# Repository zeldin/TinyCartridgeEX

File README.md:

WARNING
=======

This design is completely untested.  Since the TinyFPGA EX is not
actually available yet, there are also a number of open questions
such as:

* Does the width of the module match a standard DIL-48 socket?
  - Yes it does

* Is it OK to power the module by feeding +5V into the `Vin` pin,
  and use the `3v3` pin(s) to power auxilliary logic?  (I would
  assume so, but needs to be verified.)
  - Seems legit.  The DC/DC for 3.3V works with input voltage down
    to 3.8V, so add a protection diode with Vf < 1V.

* Are all the 42 numbered pins capable of 3.3V I/O (I sure hope so)?
  - Accoring to published schematics, VCCIO0-2 and VCCIO6-8 are all tied
  to 3.3V, which should cover all 42 pins.

TinyCartridge EX
================

The TinyCartridge EX is a carrier board for the upcoming
[TinyFPGA EX](https://www.crowdsupply.com/tinyfpga/tinyfpga-ex)
FPGA module in the form of a Commodore 64 cartridge.  All pins
on the C64 expansion port are directly available to the FPGA, with
the modification that `IO1` and `IO2` are reduced to a single
signal with NAND, and the same for `ROML` and `ROMH`.

The intention is to provide a platform for the
[super-reu](https://github.com/zeldin/super-reu) supported by
open toolchains (i.e. SymbiFlow).

Acknowledgements
----------------

The C64 expansion port and cartridge symbol and footprint were
designed by [RETRO Innovations](http://www.go4retro.com/).

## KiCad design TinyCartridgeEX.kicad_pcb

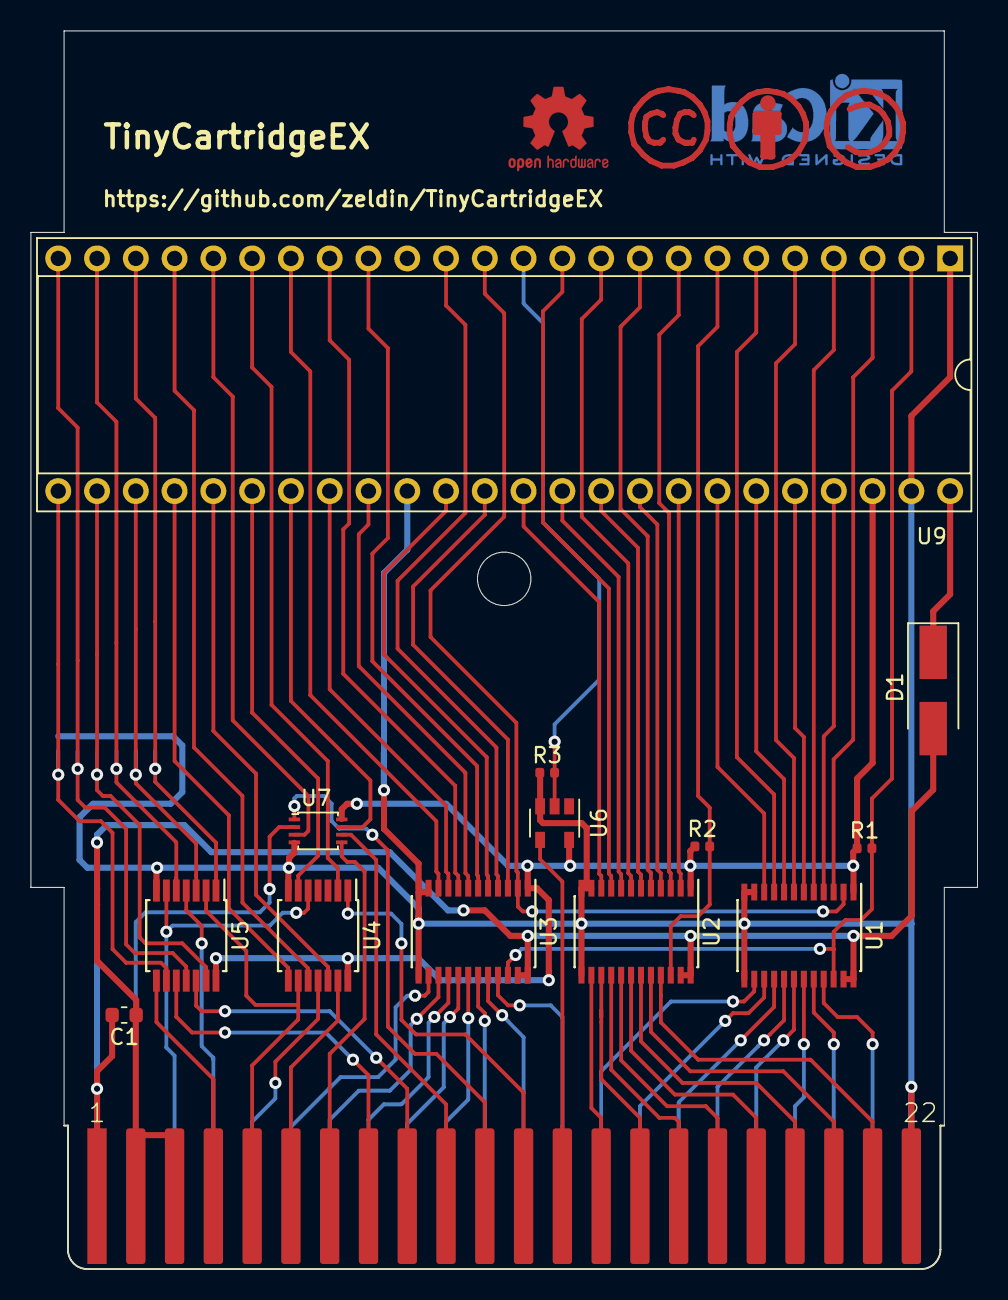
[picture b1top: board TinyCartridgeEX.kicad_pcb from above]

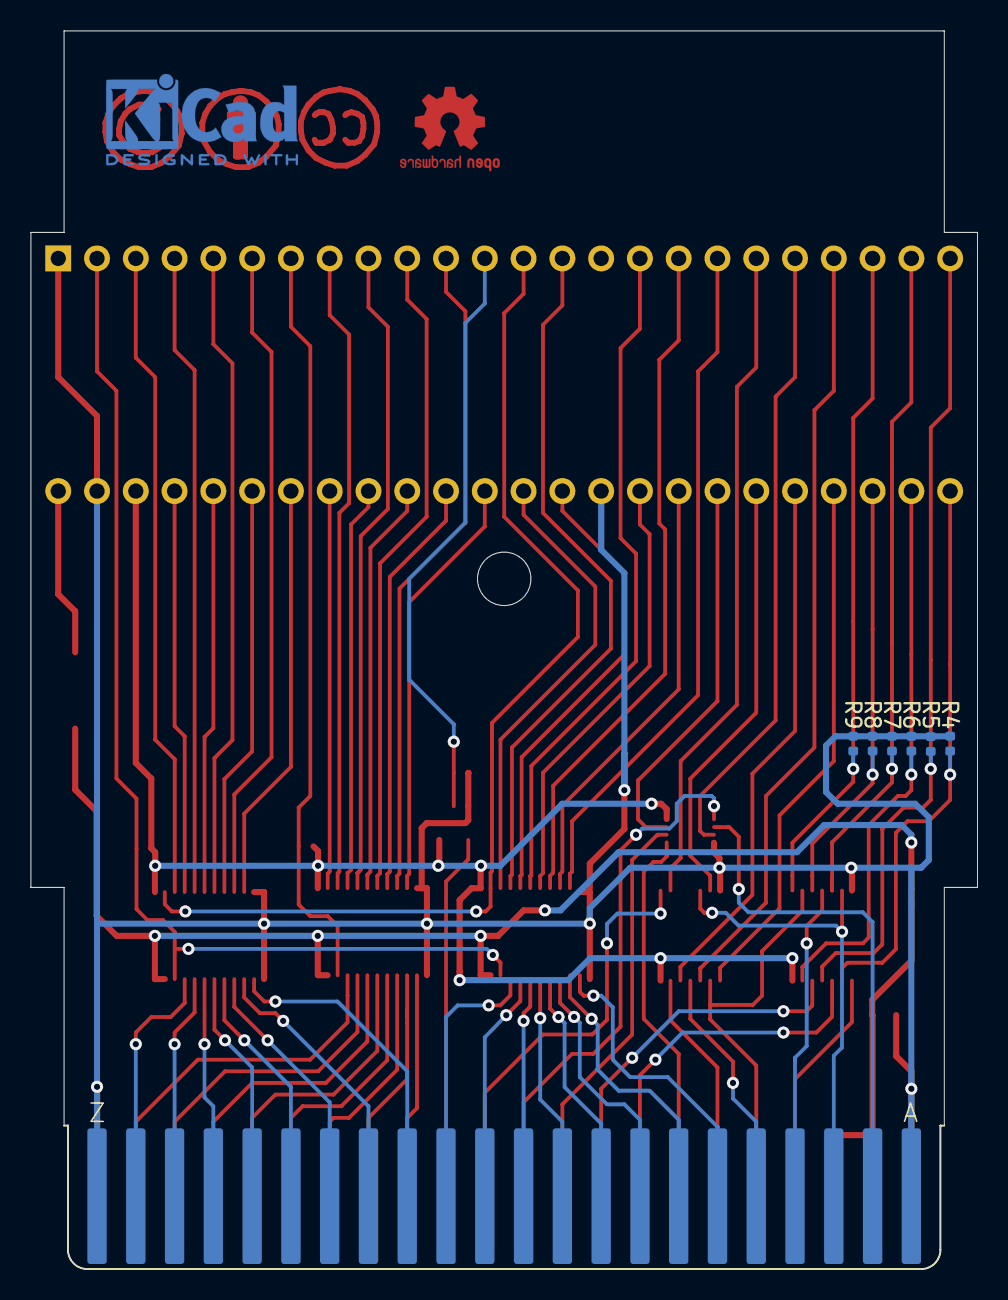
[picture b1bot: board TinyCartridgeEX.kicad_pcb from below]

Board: 2 copper layers, 62.0 x 81.1 mm, 28 parts (7 on the bottom side), 84 nets.

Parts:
C1: 0.1u; C_0603_1608Metric
CART1: CARTRIDGE_C64; CARTRIDGE_C64_GERMAN
D1: EC30QSA045; D_SMA_Handsoldering
J1, J2: Conn_01x24; PinHeader_1x24_P2.54mm_Vertical_UpsideDown
R1, R2, R3, R4, R5, R6, R7, R8, R9: 4.7k; R_0402_1005Metric
REFBY: Symbol_CC-Attribution_CopperTop_Small
REFCC: Symbol_CreativeCommons_CopperTop_Type2_Small
REFKI: KiCad-Logo2_5mm_Copper
REFOSHW: OSHW-Logo2_7.3x6mm_Copper
REFSA: Symbol_CC-ShareAlike_CopperTop_Small
U1, U2, U3: SN74LVC8T245; TSSOP-24_4.4x7.8mm_P0.65mm
U4: 74LV17A; TSSOP-14_4.4x5mm_P0.65mm
U5: 74LVC06A; TSSOP-14_4.4x5mm_P0.65mm
U6: 74LVC1G06; SOT-23-5
U7: 74LVC2G132; VSSOP-8_2.4x2.1mm_P0.5mm
U9: TinyFPGA_EX
X1: EXPANSION_PORT_C64_EDGE; MA100-22-2

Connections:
+5V: C1.1, D1.2, U1.23, U1.24, U2.23, U2.24, U3.23, U3.24, X1.2, X1.3
/Level Shifters/8: U3.21, X1.P
/Level Shifters/9: U3.20, X1.N
/Level Shifters/10: U3.19, X1.M
/Level Shifters/11: U3.18, X1.L
/Level Shifters/12: U3.17, X1.K
/Level Shifters/13: U3.16, X1.J
/Level Shifters/14: U3.15, X1.H
/Level Shifters/15: U3.14, X1.F
A0: U1.3, U9.3
A1: U1.4, U9.45
A2: U1.5, U9.4
A3: U1.6, U9.44
A4: U1.7, U9.5
A5: U1.8, U9.43
A6: U1.9, U9.6
A7: U1.10, U9.42
A8: U3.3, U9.36
A9: U3.4, U9.14
A10: U3.5, U9.35
A11: U3.6, U9.16
A12: U3.7, U9.33
A13: U3.8, U9.17
A14: U3.9, U9.32
A15: U3.10, U9.18
A_DIR: U1.2, U3.2, U9.13
A_~EN: R1.2, U1.22, U3.22, U9.2
BA: U4.2, U9.19
D0: U2.3, U9.8
D1: U2.4, U9.40
D2: U2.5, U9.9
D3: U2.6, U9.39
D4: U2.7, U9.10
D5: U2.8, U9.38
D6: U2.9, U9.11
D7: U2.10, U9.37
DMA: R3.1, U6.2, U9.12
DOTCLK: U4.12, U9.29
D_DIR: U2.2, U9.41
D_~EN: R2.1, U2.22, U9.7
EXROM: R6.1, U5.13, U9.26
GAME: R5.1, U5.11, U9.24
GND: C1.2, R3.2, R4.2, R5.2, R6.2, R7.2, R8.2, R9.2, U1.11, U1.12, U1.13, U2.11, U2.12, U2.13, U3.11, U3.12, U3.13, U4.7, U5.7, U6.3, U7.4, U9.1, U9.34, U9.47, X1.1, X1.22, X1.A, X1.Z
IO12: U7.3, U9.20
IRQ_OUT: R4.1, U5.9, U9.25
NMI_OUT: R8.1, U5.3, U9.27
unnamed: D1.1, U9.48
unnamed: U1.14, X1.R
unnamed: U1.15, X1.S
unnamed: U1.16, X1.T
unnamed: U1.17, X1.U
unnamed: U1.18, X1.V
unnamed: U1.19, X1.W
unnamed: U1.20, X1.X
unnamed: U1.21, X1.Y
unnamed: U2.14, X1.14
unnamed: U2.15, X1.15
unnamed: U2.16, X1.16
unnamed: U2.17, X1.17
unnamed: U2.18, X1.18
unnamed: U2.19, X1.19
unnamed: U2.20, X1.20
unnamed: U2.21, X1.21
unnamed: U4.1, X1.12
unnamed: U4.5, U5.6, X1.C
unnamed: U4.9, U5.2, X1.5
unnamed: U4.11, X1.E
unnamed: U4.13, X1.6
unnamed: U5.4, X1.D
unnamed: U5.8, X1.4
unnamed: U5.10, X1.8
unnamed: U5.12, X1.9
unnamed: U6.4, X1.13
unnamed: U7.1, X1.11
unnamed: U7.2, X1.B
unnamed: U7.5, X1.7
unnamed: U7.6, X1.10
PHI2: U4.10, U9.21
RESET_IN: U4.6, U9.30
RESET_OUT: R7.1, U5.5, U9.23
ROMLH: U7.7, U9.31
RW_IN: U4.8, U9.28
RW_OUT: R9.1, U5.1, U9.22
VCC: R1.1, R2.2, U1.1, U2.1, U3.1, U4.14, U5.14, U6.5, U7.8, U9.46

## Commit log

2020-02-09 Remove superfluous Schmitt buffers on NAND inputs
2020-02-09 Set correct logic families and add Mouser part# and pricing for BOM
2020-02-09 Slightly cleanup schematic page
2020-02-09 Remove funky drill hole from cartridge footprint
2020-02-09 Fix PCB outline and add some logos/text
2020-02-09 Add CC-BY-SA license
2020-02-09 Added a readme
2020-02-10 Move SN74AVC8T245PW symbol into buffers.lib
    It turns out some version of Logic_LevelTranslator.lib doesn't have
    it.
2020-02-11 Replace cartridge footprint
    The new footprint is created based on the technical drawings
    found here: http://wiki.icomp.de/wiki/C64_Cartridge_Cases
2020-02-19 Insert a 3D model of the TinyFPGA EX module
2020-02-20 Add diode to Vin
2020-02-21 Fix badly placed trace
2020-03-01 BOM update
